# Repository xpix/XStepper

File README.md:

XStepper
=============

A new Solution with Grbl Firmware to use cnc mills or 3d printers.

created by Frank Herrmann (xpix), Godsplan

---------------

The XStepper includes the following features:

- ATMega328u (DIL Package)
- USB Connection using USB-FTDI
- Opto-Couplers for USB Connection
- ICSP-Connector for flashing the firmware
- GRBL Firmware (v0.8) and GRBL Pinout
- Connector for External Buttons for spindle, reset, etc...
- Support for four Pololu A4988 or Pololu DRV8825 Modules
- Supports dual-Y motion
- Supports cooling fan
- Supports XYZ-Limit in extra pinheader
- LED's for every axis
- LED's for every Limit
- Power LED
- AK500 Screw terminal for Steppers
- Connector for Bluetooth TTL Modules

---------------
v0.9.1

- add optional pullup resistors (1k/5V) for Hallo Sesnor switches (Cherry MP101401)
   http://www.cherrycorp.com/english/sensors/pdf/MP1014_Series.pdf

v0.9 

- created schema files
- created .brd

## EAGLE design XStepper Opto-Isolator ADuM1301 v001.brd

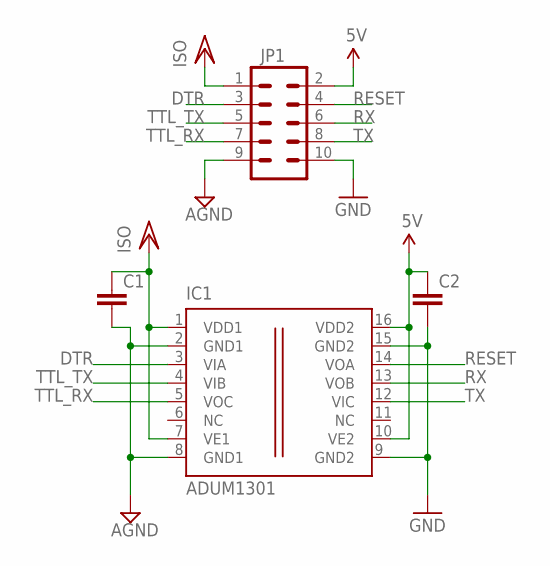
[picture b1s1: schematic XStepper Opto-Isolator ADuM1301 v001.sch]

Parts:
C1, C2: CAP0805; 0805
IC1: ADUM1301; SO-16W
JP1: M05X2PTH; AVR_ICSP

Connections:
5V: C2.1, IC1.10 (VE2), IC1.16 (VDD2), JP1.2
AGND: C1.2, IC1.2 (GND1), IC1.8 (GND1), JP1.9
DTR: IC1.3 (VIA), JP1.3
GND: C2.2, IC1.9 (GND2), IC1.15 (GND2), JP1.10
RESET: IC1.14 (VOA), JP1.4
RX: IC1.13 (VOB), JP1.6
TTL_RX: IC1.5 (VOC), JP1.7
TTL_TX: IC1.4 (VIB), JP1.5
TX: IC1.12 (VIC), JP1.8
VCC/2: C1.1, IC1.1 (VDD1), IC1.7 (VE1), JP1.1

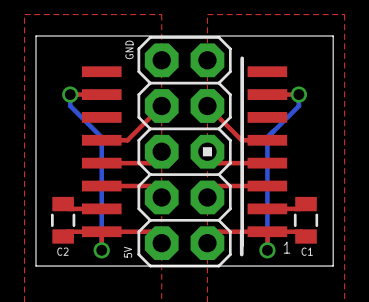
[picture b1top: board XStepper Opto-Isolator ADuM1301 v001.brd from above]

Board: 2 copper layers, 16.5 x 12.8 mm, 4 parts (0 on the bottom side), 10 nets.

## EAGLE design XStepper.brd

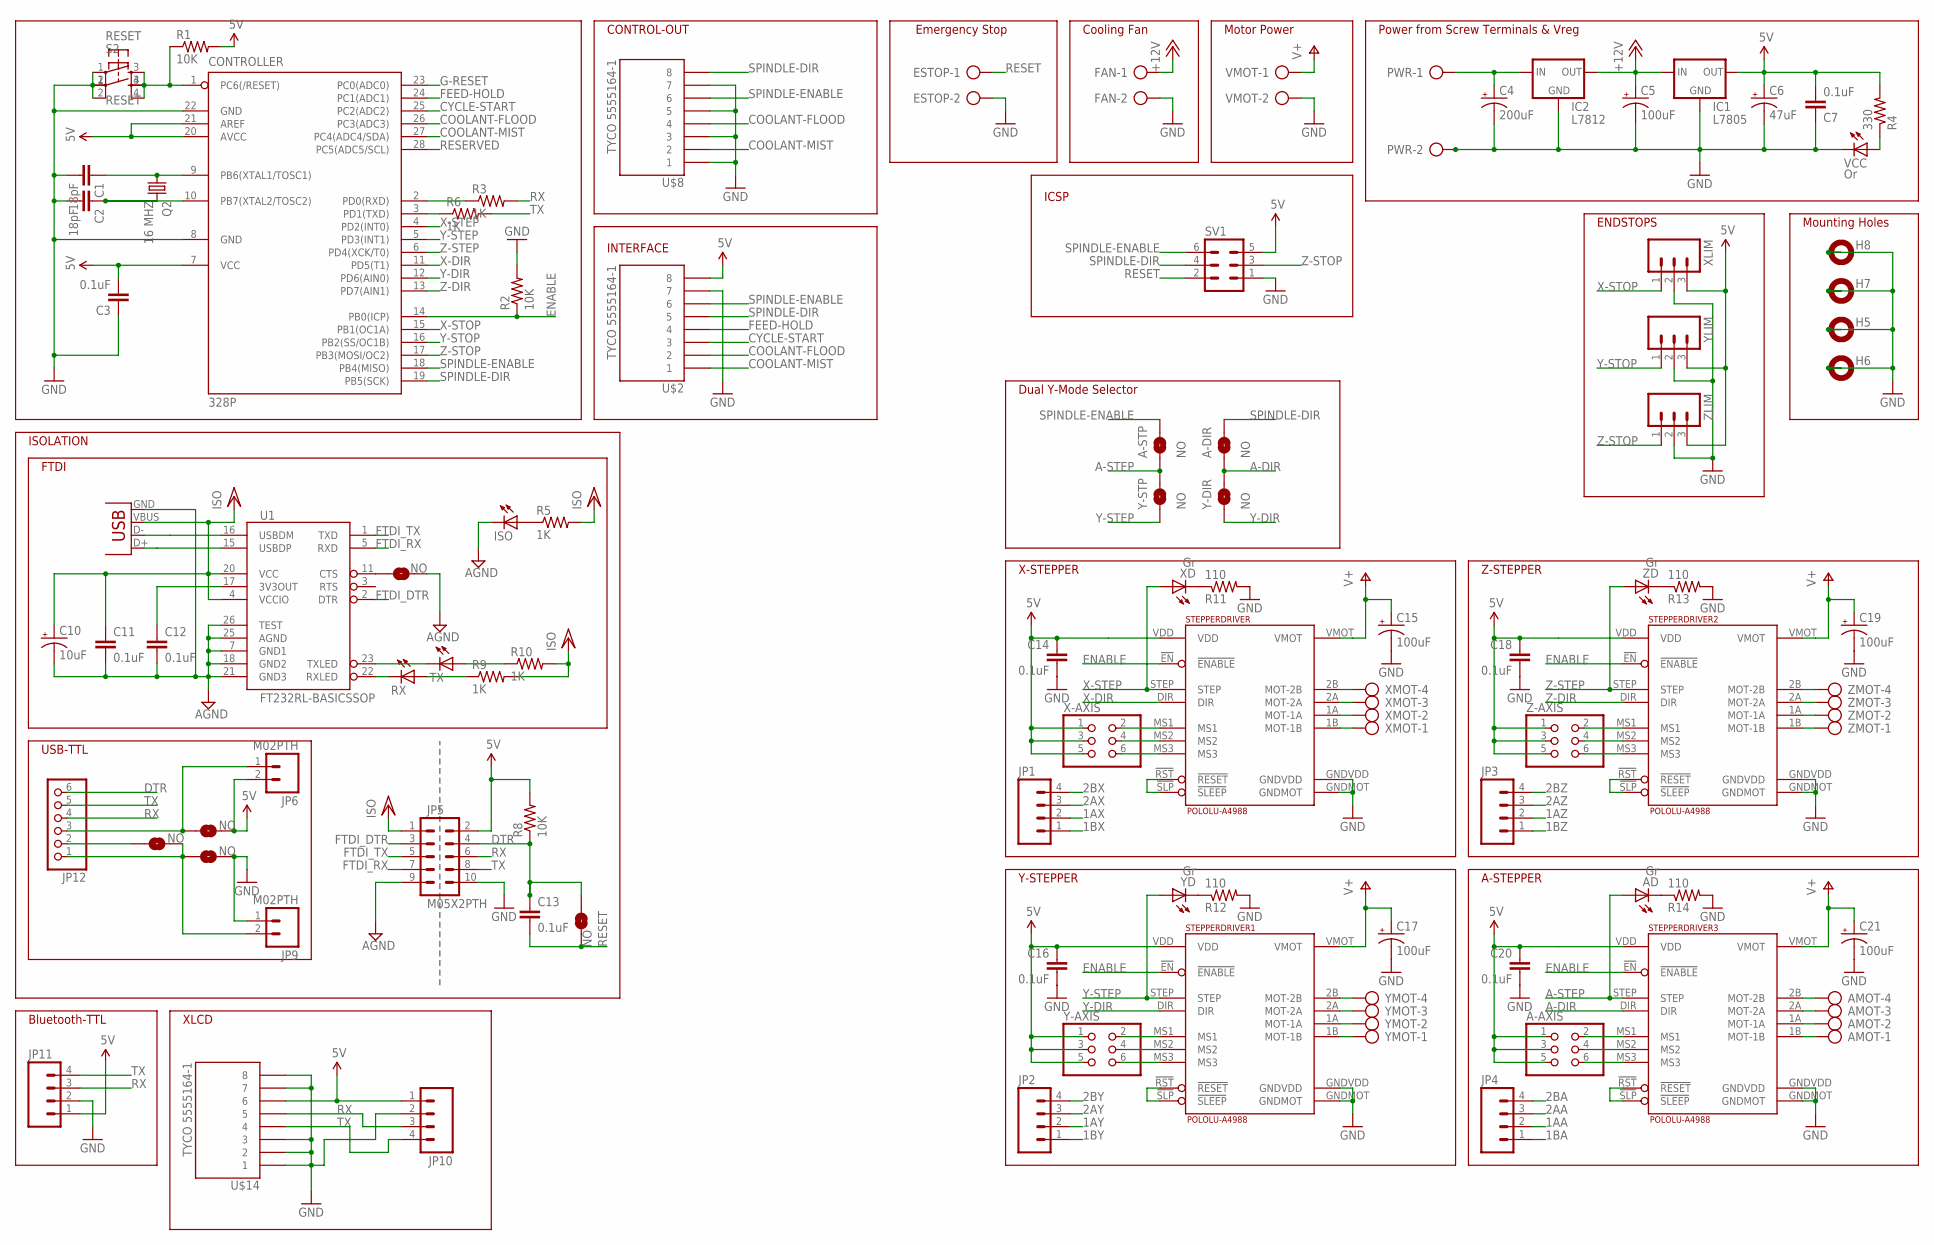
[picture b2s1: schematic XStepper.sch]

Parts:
5V: NO; SJ_2S-NO
328P: CONTROLLER; DIL28-3
A-AXIS: PINHD-2X3; 2X03
A-DIR: NO; SJ_2S-NO
A-STP: NO; SJ_2S-NO
AD: Gr; LED3MM
AMOT: AK500/4
C1, C2: 18pF; C025-025X050
C3, C7, C13, C14, C16, C18, C20: 0.1uF; C025-025X050
C4: 200uF; E3,5-8
C5: 100uF; E2,5-6
C6: 47uF; E2,5-6
C10: 10uF; EIA3216
C11, C12: 0.1uF; 1206
C15, C17, C19, C21: 100uF; E3,5-8
CTS: NO; SJ_2S-NO
CTS-FTDI: NO; SJ_2S-NO
DTR: NO; SJ_2S-NO
ESTOP: AK500/2
FAN: AK500/2
GND: NO; SJ_2S-NO
H5, H6, H7, H8: MOUNT-PAD-ROUND3.6; 3,6-PAD
IC1: L7805; TO220-IGO
IC2: L7812; TO220-IGO
ISO: LED3MM
JP1, JP2, JP3, JP4, JP10, JP11: M04PTH; 1X04
JP5: M05X2PTH; AVR_ICSP
JP6, JP9: M02PTH; 1X02
JP7: USBSMD; USB-MINIB
JP12: PINHD-1X6; 1X06
PWR: AK500/2
Q2: 16 MHZ; HC49/S
R1, R2, R8: 10K; AXIAL-0.3
R3, R6: 1K; AXIAL-0.3
R4: 330; AXIAL-0.3
R5, R9, R10: 1K; 1206
R11, R12, R13, R14: 110; AXIAL-0.3
RESET: RESET; TACTILE-PTH
RX: LED3MM
S2: TAC_SWITCHSMD; TACTILE_SWITCH_SMD
STEPPERDRIVER, STEPPERDRIVER1, STEPPERDRIVER2, STEPPERDRIVER3: POLOLU-A4988; POLOLU-ALLEGRO-PTH
SV1: ML6
TX: LED3MM
U1: FT232RL-BASICSSOP; SSOP28DB
U$2, U$8, U$14: TYCO 5555164-1; RJ45-8
VCC: Or; LED3MM
VMOT: AK500/2
X-AXIS: PINHD-2X3; 2X03
XD: Gr; LED3MM
XLIM: M03POLAR; MOLEX-1X3
XMOT: AK500/4
Y-AXIS: PINHD-2X3; 2X03
Y-DIR: NO; SJ_2S-NO
Y-STP: NO; SJ_2S-NO
YD: Gr; LED3MM
YLIM: M03POLAR; MOLEX-1X3
YMOT: AK500/4
Z-AXIS: PINHD-2X3; 2X03
ZD: Gr; LED3MM
ZLIM: M03POLAR; MOLEX-1X3
ZMOT: AK500/4

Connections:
1AA: AMOT.2, JP4.2, STEPPERDRIVER3.1A (MOT-1A)
1AX: JP1.2, STEPPERDRIVER.1A (MOT-1A), XMOT.2
1AY: JP2.2, STEPPERDRIVER1.1A (MOT-1A), YMOT.2
1AZ: JP3.2, STEPPERDRIVER2.1A (MOT-1A), ZMOT.2
1BA: AMOT.1, JP4.1, STEPPERDRIVER3.1B (MOT-1B)
1BX: JP1.1, STEPPERDRIVER.1B (MOT-1B), XMOT.1
1BY: JP2.1, STEPPERDRIVER1.1B (MOT-1B), YMOT.1
1BZ: JP3.1, STEPPERDRIVER2.1B (MOT-1B), ZMOT.1
2AA: AMOT.3, JP4.3, STEPPERDRIVER3.2A (MOT-2A)
2AX: JP1.3, STEPPERDRIVER.2A (MOT-2A), XMOT.3
2AY: JP2.3, STEPPERDRIVER1.2A (MOT-2A), YMOT.3
2AZ: JP3.3, STEPPERDRIVER2.2A (MOT-2A), ZMOT.3
2BA: AMOT.4, JP4.4, STEPPERDRIVER3.2B (MOT-2B)
2BX: JP1.4, STEPPERDRIVER.2B (MOT-2B), XMOT.4
2BY: JP2.4, STEPPERDRIVER1.2B (MOT-2B), YMOT.4
2BZ: JP3.4, STEPPERDRIVER2.2B (MOT-2B), ZMOT.4
5V: 5V.2, 328P.7 (VCC), 328P.20 (AVCC), 328P.21 (AREF), A-AXIS.1, A-AXIS.3, A-AXIS.5, C3.2, C6.+, C7.2, C14.1, C16.1, C18.1, C20.1, IC1.OUT, JP5.2, JP6.2, JP10.1, JP11.1, R1.P$2 (2), R4.P$2 (2), R8.P$2 (2), STEPPERDRIVER.VDD, STEPPERDRIVER1.VDD, STEPPERDRIVER2.VDD, STEPPERDRIVER3.VDD, SV1.5, U$2.8, U$14.6, X-AXIS.1, X-AXIS.3, X-AXIS.5, XLIM.3, Y-AXIS.1, Y-AXIS.3, Y-AXIS.5, YLIM.3, Z-AXIS.1, Z-AXIS.3, Z-AXIS.5, ZLIM.3
+12V: C5.+, FAN.1, IC1.IN, IC2.OUT
A-DIR: A-DIR.1, STEPPERDRIVER3.DIR, Y-DIR.2
A-STEP: A-STP.1, AD.A, STEPPERDRIVER3.STEP, Y-STP.2
AGND: C10.C (-), C11.2, C12.2, CTS-FTDI.2, ISO.K (C), JP5.9, JP7.GND, U1.7 (GND1), U1.18 (GND2), U1.21 (GND3), U1.25 (AGND), U1.26 (TEST)
COOLANT-FLOOD: 328P.26 (PC3(ADC3)), U$2.2, U$8.4
COOLANT-MIST: 328P.27 (PC4(ADC4/SDA)), U$2.1, U$8.2
CYCLE-START: 328P.25 (PC2(ADC2)), U$2.3
DTR: C13.1, DTR.1, JP5.4, JP12.6, R8.P$1 (1)
ENABLE: 328P.14 (PB0(ICP)), R2.P$1 (1), STEPPERDRIVER.!EN (!ENABLE), STEPPERDRIVER1.!EN (!ENABLE), STEPPERDRIVER2.!EN (!ENABLE), STEPPERDRIVER3.!EN (!ENABLE)
FEED-HOLD: 328P.24 (PC1(ADC1)), U$2.4
FTDI_DTR: JP5.3, U1.2 (DTR)
FTDI_RX: JP5.7, U1.5 (RXD)
FTDI_TX: JP5.5, U1.1 (TXD)
G-RESET: 328P.23 (PC0(ADC0))
GND: 328P.8 (GND), 328P.22 (GND), C1.2, C2.2, C3.1, C4.-, C5.-, C6.-, C7.1, C14.2, C15.-, C16.2, C17.-, C18.2, C19.-, C20.2, C21.-, ESTOP.2, FAN.2, GND.2, H5.B3,6, H6.B3,6, H7.B3,6, H8.B3,6, IC1.GND, IC2.GND, JP5.10, JP9.1, JP10.2, JP11.2, PWR.2, R2.P$2 (2), R11.P$2 (2), R12.P$2 (2), R13.P$2 (2), R14.P$2 (2), RESET.1, RESET.2, S2.1, S2.2, STEPPERDRIVER.GNDMOT, STEPPERDRIVER.GNDVDD, STEPPERDRIVER1.GNDMOT, STEPPERDRIVER1.GNDVDD, STEPPERDRIVER2.GNDMOT, STEPPERDRIVER2.GNDVDD, STEPPERDRIVER3.GNDMOT, STEPPERDRIVER3.GNDVDD, SV1.1, U$2.7, U$8.1, U$8.3, U$8.5, U$8.7, U$14.1, U$14.2, U$14.3, U$14.7, U$14.8, VCC.K (C), VMOT.2, XLIM.2, YLIM.2, ZLIM.2
unnamed: C12.1, U1.17 (3V3OUT)
unnamed: JP7.D+, U1.15 (USBDP)
unnamed: JP7.D-, U1.16 (USBDM)
unnamed: ISO.A, R5.1
unnamed: STEPPERDRIVER.!RST (!RESET), STEPPERDRIVER.!SLP (!SLEEP)
unnamed: STEPPERDRIVER.MS1, X-AXIS.2
unnamed: STEPPERDRIVER.MS2, X-AXIS.4
unnamed: STEPPERDRIVER.MS3, X-AXIS.6
unnamed: 328P.2 (PD0(RXD)), R3.P$1 (1)
unnamed: CTS.1, JP12.2
unnamed: TX.K (C), U1.23 (TXLED)
unnamed: RX.K (C), U1.22 (RXLED)
unnamed: STEPPERDRIVER1.!RST (!RESET), STEPPERDRIVER1.!SLP (!SLEEP)
unnamed: STEPPERDRIVER1.MS1, Y-AXIS.2
unnamed: STEPPERDRIVER1.MS2, Y-AXIS.4
unnamed: STEPPERDRIVER1.MS3, Y-AXIS.6
unnamed: R9.1, RX.A
unnamed: R10.1, TX.A
unnamed: CTS-FTDI.1, U1.11 (CTS)
unnamed: R11.P$1 (1), XD.K (C)
unnamed: STEPPERDRIVER2.!RST (!RESET), STEPPERDRIVER2.!SLP (!SLEEP)
unnamed: STEPPERDRIVER2.MS1, Z-AXIS.2
unnamed: STEPPERDRIVER2.MS2, Z-AXIS.4
unnamed: STEPPERDRIVER2.MS3, Z-AXIS.6
unnamed: R12.P$1 (1), YD.K (C)
unnamed: R13.P$1 (1), ZD.K (C)
unnamed: AD.K (C), R14.P$1 (1)
unnamed: STEPPERDRIVER3.!RST (!RESET), STEPPERDRIVER3.!SLP (!SLEEP)
unnamed: A-AXIS.2, STEPPERDRIVER3.MS1
unnamed: A-AXIS.4, STEPPERDRIVER3.MS2
unnamed: A-AXIS.6, STEPPERDRIVER3.MS3
unnamed: 328P.9 (PB6(XTAL1/TOSC1)), C1.1, Q2.1
unnamed: 328P.10 (PB7(XTAL2/TOSC2)), C2.1, Q2.2
unnamed: 328P.3 (PD1(TXD)), R6.P$1 (1)
unnamed: 5V.1, JP6.1, JP12.3
unnamed: R4.P$1 (1), VCC.A
unnamed: CTS.2, GND.1, JP9.2, JP12.1
RESERVED: 328P.28 (PC5(ADC5/SCL))
RESET: 328P.1 (PC6(/RESET)), C13.2, DTR.2, ESTOP.1, R1.P$1 (1), RESET.3, RESET.4, S2.3, S2.4, SV1.2
RX: JP5.6, JP10.3, JP11.3, JP12.4, R3.P$2 (2), U$14.5
SPINDLE-DIR: 328P.19 (PB5(SCK)), A-DIR.2, SV1.4, U$2.5, U$8.8
SPINDLE-ENABLE: 328P.18 (PB4(MISO)), A-STP.2, SV1.6, U$2.6, U$8.6
TX: JP5.8, JP10.4, JP11.4, JP12.5, R6.P$2 (2), U$14.4
V+: C15.+, C17.+, C19.+, C21.+, STEPPERDRIVER.VMOT, STEPPERDRIVER1.VMOT, STEPPERDRIVER2.VMOT, STEPPERDRIVER3.VMOT, VMOT.1
VCC/2: C10.A (+), C11.1, JP5.1, JP7.VBUS, R5.2, R9.2, R10.2, U1.4 (VCCIO), U1.20 (VCC)
VIN: C4.+, IC2.IN, PWR.1
X-DIR: 328P.11 (PD5(T1)), STEPPERDRIVER.DIR
X-STEP: 328P.4 (PD2(INT0)), STEPPERDRIVER.STEP, XD.A
X-STOP: 328P.15 (PB1(OC1A)), XLIM.1
Y-DIR: 328P.12 (PD6(AIN0)), STEPPERDRIVER1.DIR, Y-DIR.1
Y-STEP: 328P.5 (PD3(INT1)), STEPPERDRIVER1.STEP, Y-STP.1, YD.A
Y-STOP: 328P.16 (PB2(SS/OC1B)), YLIM.1
Z-DIR: 328P.13 (PD7(AIN1)), STEPPERDRIVER2.DIR
Z-STEP: 328P.6 (PD4(XCK/T0)), STEPPERDRIVER2.STEP, ZD.A
Z-STOP: 328P.17 (PB3(MOSI/OC2)), SV1.3, ZLIM.1

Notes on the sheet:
X-STEPPER
Y-STEPPER
Z-STEPPER
Power from Screw Terminals & Vreg
A-STEPPER
Dual Y-Mode Selector
ISOLATION
Cooling Fan
Mounting Holes
USB-TTL
INTERFACE
Bluetooth-TTL
Emergency Stop
ENDSTOPS
FTDI
Motor Power
CONTROL-OUT
ICSP
XLCD

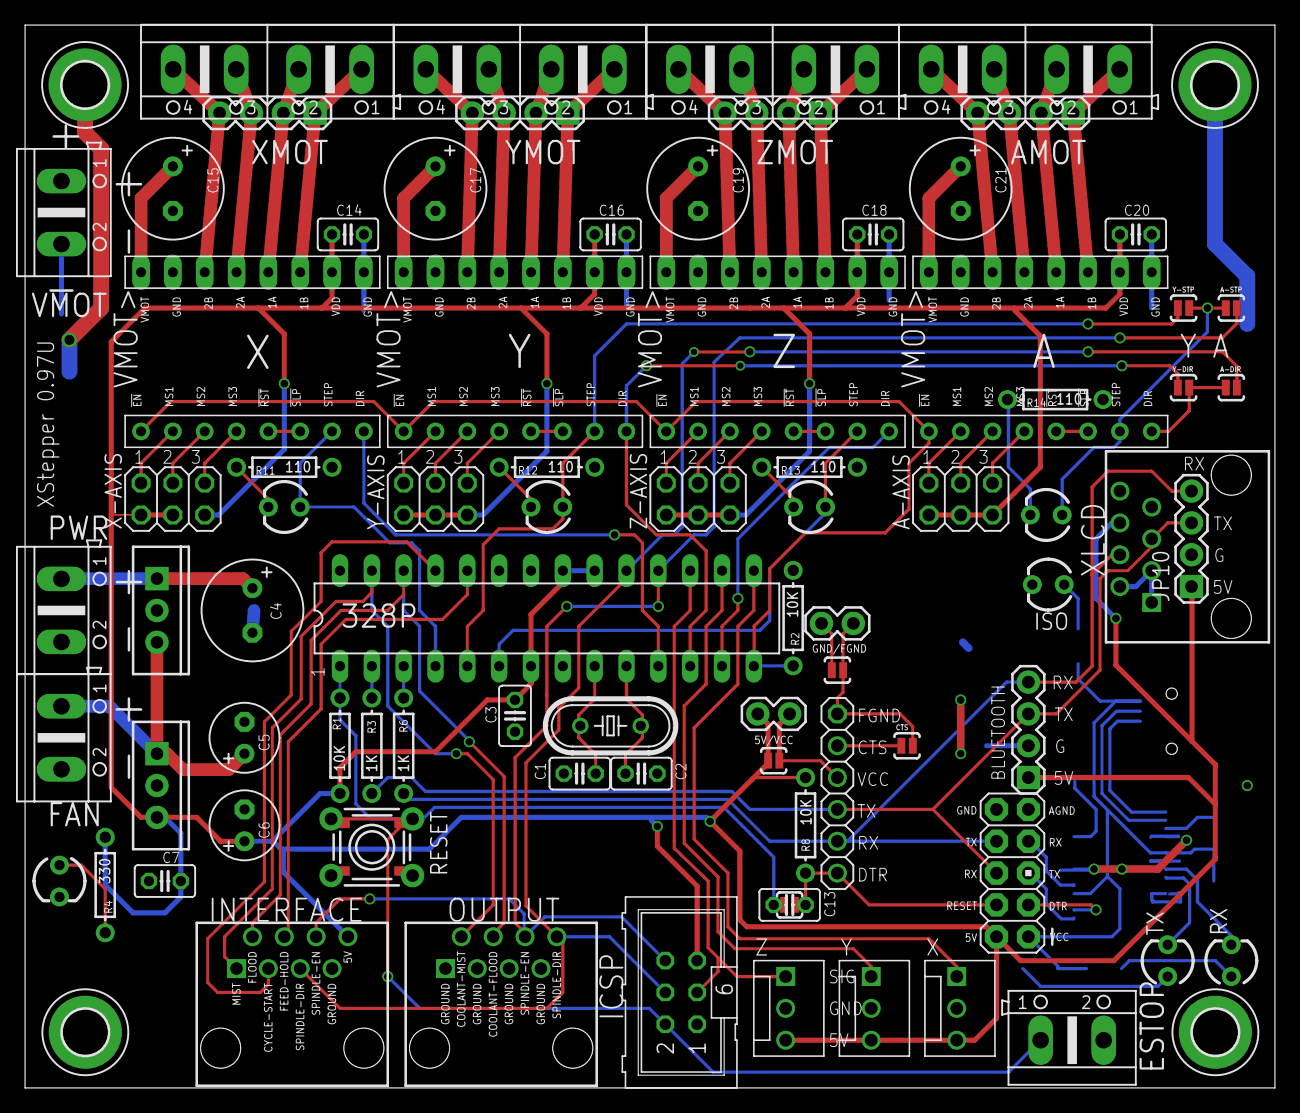
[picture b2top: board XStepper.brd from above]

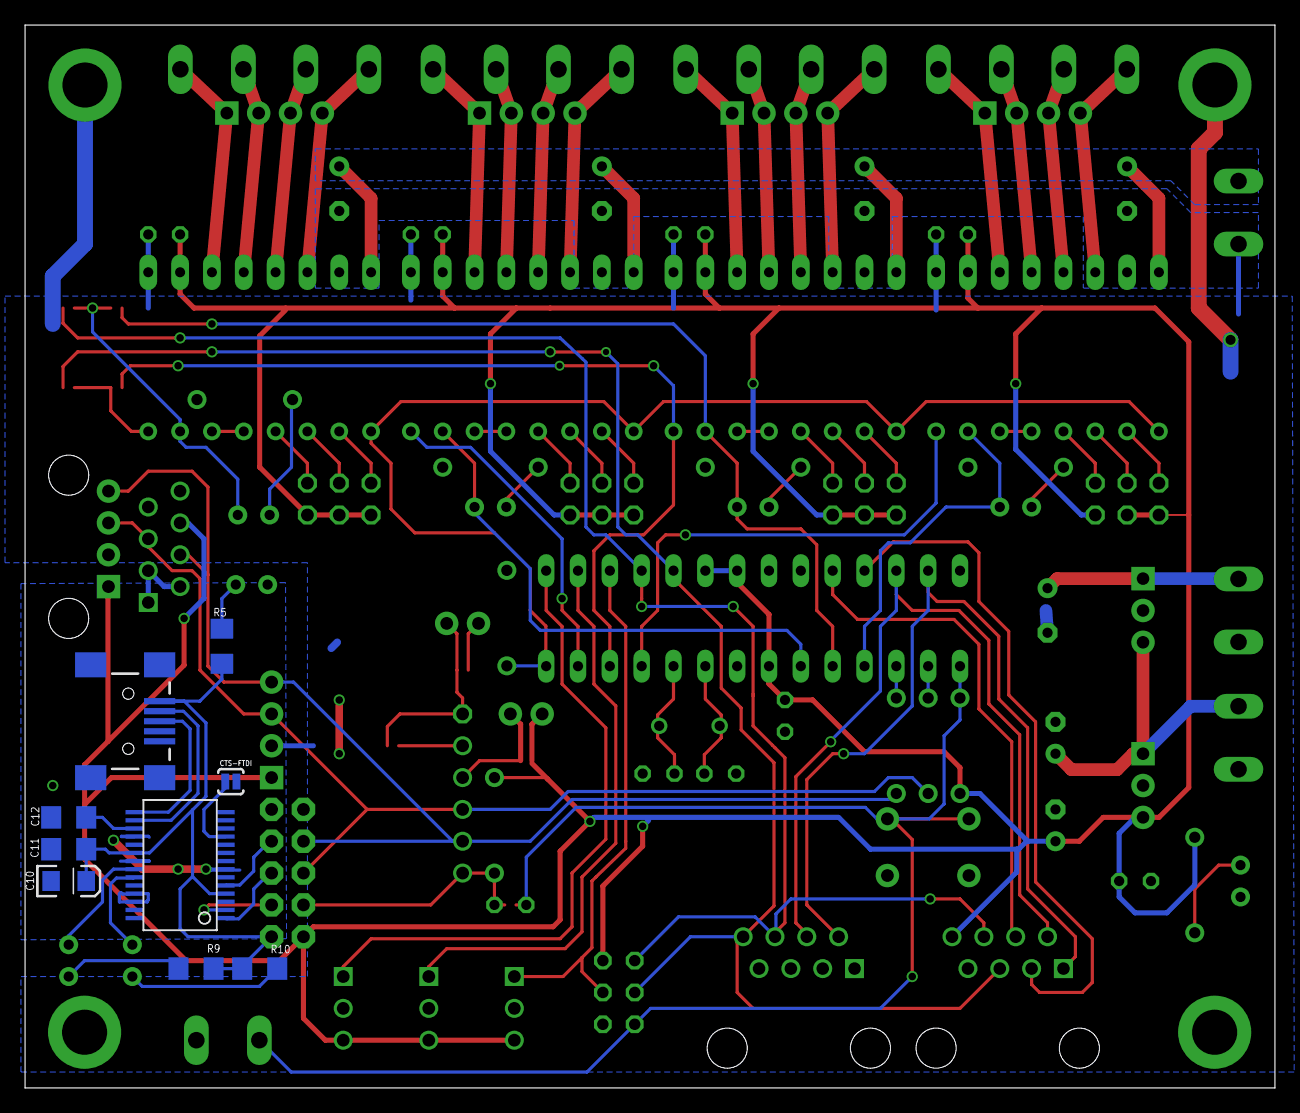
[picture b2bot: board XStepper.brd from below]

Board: 2 copper layers, 99.7 x 84.8 mm, 94 parts (9 on the bottom side), 85 nets.

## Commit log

2013-05-10 initial fork from GRBLMainboard
2013-05-10 Change Readme
2013-05-21 add Bluetooth Connector
    Add connector for Bluetooth TTL Module.
2013-05-24 Remove unused files
    - also add comment to Readme.
2013-05-24 refresh sketchup file
2013-06-03 add pullup resistors for Hallo Sensor switches (Cherry MP101401)
2013-07-19 Bugfree version from 0.9 to produce in ITEAD
    Version 0.91 from Matt to produce without bugs
2013-07-30 - change header ICSP
    - more space between caps at 7805
    - add VCC area on top to save wires
2013-08-01 - Bugfix COMSERIAL
    change pins on comserial block
    remove some unused files
2013-08-09 - bugfix diode
    - add new autorouting
    - move emergency screw near to cpu
2013-08-14 - add VMOT sign to driver for users
    - remove circle for pod cuz they are different on drivers
2013-08-19 - some changes for community
    * move screw terminals for motors 1mm up for bigger caps
    * add a 12V voltage regulator for fan
    * replace powerled resitor to a small one
2013-08-20 - bigger vmot caps 8mm
2013-08-22 - add 7812 regulator for fan and main 5V voltage regulator
    - change c10 to small cap cuz he get only 12v with new regulator
2013-09-19 - last design from matt
    - correct some issues
    - run all eagle tests
2013-09-19 - remove old gerber files
2013-10-09 - some changes from matt and produce in fab 0.95
2013-10-30 - gerber files for ITEAD 0.96
    - new pic for docs
2013-12-10 - version 0.97 to fab
    *On-board USB in now in the bottom of the board
    *USB isolation header moved.
    *Bluetooth header moved
    *Bluetooth dip/jumpers removed - bluetooth is always-on
    *FTDI header moved
    *FTDI now can be tied to 5V and GND for isolation or to forego isolation

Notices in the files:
parts and their libraries:
SparkFun-Connectors: Licensing: CC v3.0 Share-Alike You are welcome to use this library for commercial purposes.
